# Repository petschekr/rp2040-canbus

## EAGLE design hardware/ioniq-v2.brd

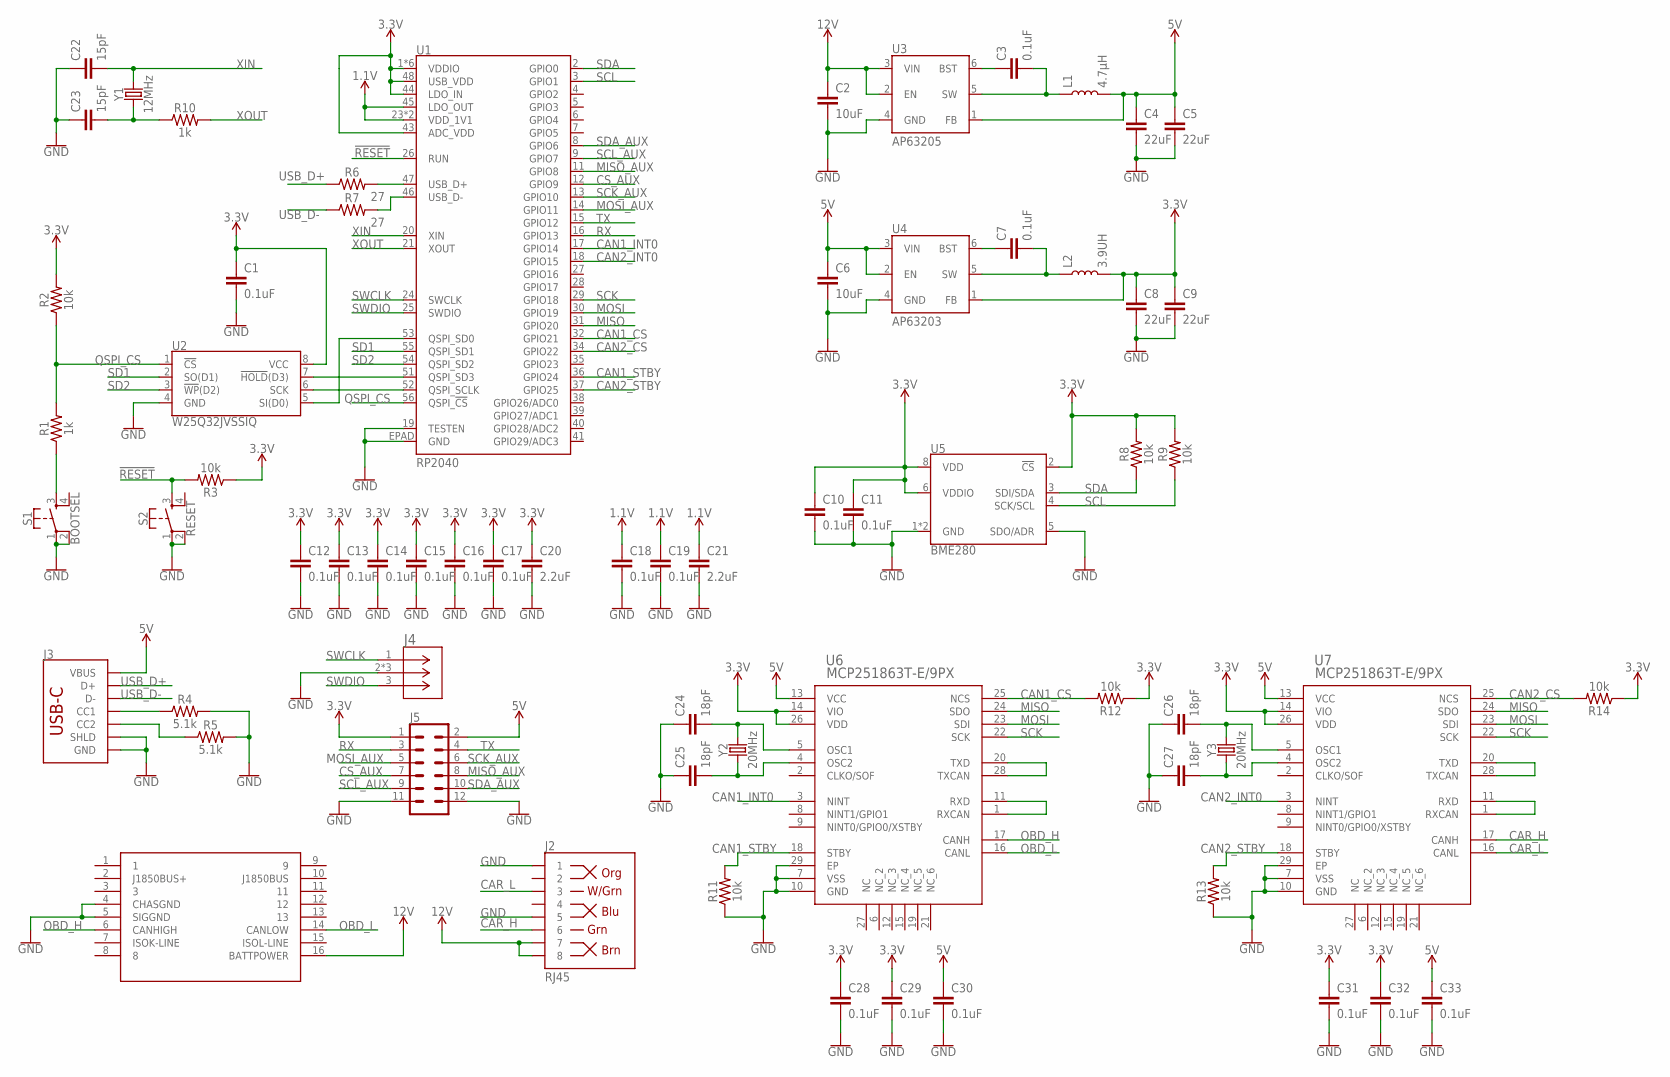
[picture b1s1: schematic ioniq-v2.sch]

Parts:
C1, C3, C7, C10, C11, C12, C13, C14, C15, C16, C17, C18, C19, C28, C29, C30, C31, C32, C33: 0.1uF; 0603
C2, C6: 10uF; 0805
C4, C5, C8, C9: 22uF; 0603
C20, C21: 2.2uF; 0603
C22, C23: 15pF; 0603
C24, C25, C26, C27: 18pF; 0603
J1: OBDII
J2: RJ45; RJ45-8
J3: USB_C_2-LAYER_PADS; USB-C-16P-2LAYER-PADS
J4: BM03B-SRSS-TB(LF)(SN); CONN_BM03B-SRSS-TB(LF)(SN)_JST
J5: 2X6 FEMALE; 2X6
L1: 4.7μH; INDUCTOR_4X4MM
L2: 3.9UH; INDUCTOR_3.9UH
R1, R10: 1k; 0603
R2, R3, R8, R9, R11, R12, R13, R14: 10k; 0603
R4, R5: 5.1k; 0603
R6, R7: 27; 0603
S1: BOOTSEL; TACTILE_SWITCH_SMD_4.6X2.8MM
S2: RESET; TACTILE_SWITCH_SMD_4.6X2.8MM
U1: RP2040; QFN-56
U2: W25Q32JVSSIQ; SOIC-8
U3: AP63205; SOT23-6
U4: AP63203; SOT23-6
U5: BME280; LGA-8-2.5X2.5
U6, U7: MCP251863T-E/9PX; VQFN28_9PX_3P25X3P25EPAD_MCH
Y1: 12MHz; CRYSTAL-SMD-3.2X2.5MM
Y2, Y3: 20MHz; CRYSTAL-SMD-3.2X2.5MM

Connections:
1.1V: C18.1, C19.1, C21.1, U1.23 (VDD_1V1), U1.45 (LDO_OUT), U1.50 (VDD_1V1)
3.3V: C1.1, C8.1, C9.1, C10.1, C11.1, C12.1, C13.1, C14.1, C15.1, C16.1, C17.1, C20.1, C28.1, C29.1, C31.1, C32.1, J5.1, L2.P$2 (2), R2.2, R3.1, R8.2, R9.2, R12.1, R14.1, U1.1 (VDDIO), U1.10 (VDDIO), U1.22 (VDDIO), U1.33 (VDDIO), U1.42 (VDDIO), U1.43 (ADC_VDD), U1.44 (LDO_IN), U1.48 (USB_VDD), U1.49 (VDDIO), U2.8 (VCC), U4.1 (FB), U5.2 (!CS), U5.6 (VDDIO), U5.8 (VDD), U6.14 (VIO), U6.26 (VDD), U7.14 (VIO), U7.26 (VDD)
5V: C4.1, C5.1, C6.1, C30.1, C33.1, J3.VBUS1 (VBUS), J3.VBUS2 (VBUS), J5.2, L1.P$2 (2), U3.1 (FB), U4.2 (EN), U4.3 (VIN), U6.13 (VCC), U7.13 (VCC)
12V: C2.1, J1.16 (BATTPOWER), J2.7, J2.8, U3.2 (EN), U3.3 (VIN)
!RESET: R3.2, S2.3, U1.26 (RUN)
CAN1_CS: R12.2, U1.32 (GPIO21), U6.25 (NCS)
CAN1_INT0: U1.17 (GPIO14), U6.3 (NINT)
CAN1_STBY: R11.2, U1.36 (GPIO24), U6.18 (STBY)
CAN2_CS: R14.2, U1.34 (GPIO22), U7.25 (NCS)
CAN2_INT0: U1.18 (GPIO15), U7.3 (NINT)
CAN2_STBY: R13.2, U1.37 (GPIO25), U7.18 (STBY)
CAR_H: J2.6, U7.17 (CANH)
CAR_L: J2.3, U7.16 (CANL)
CS_AUX: J5.7, U1.12 (GPIO9)
GND: C1.2, C2.2, C4.2, C5.2, C6.2, C8.2, C9.2, C10.2, C11.2, C12.2, C13.2, C14.2, C15.2, C16.2, C17.2, C18.2, C19.2, C20.2, C21.2, C22.1, C23.1, C24.1, C25.1, C26.1, C27.1, C28.2, C29.2, C30.2, C31.2, C32.2, C33.2, J1.4 (CHASGND), J1.5 (SIGGND), J2.1, J2.5, J3.GND, J3.GND2 (GND), J3.SHLD1 (SHLD), J3.SHLD2 (SHLD), J3.SHLD3 (SHLD), J3.SHLD4 (SHLD), J4.2, J4.4 (2), J4.5 (2), J5.11, J5.12, R4.2, R5.2, R11.1, R13.1, S1.1, S1.2, S2.1, S2.2, U1.19 (TESTEN), U1.EPAD (GND), U2.4 (GND), U3.4 (GND), U4.4 (GND), U5.1 (GND), U5.5 (SDO/ADR), U5.7 (GND), U6.7 (VSS), U6.10 (GND), U6.29 (EP), U7.7 (VSS), U7.10 (GND), U7.29 (EP)
MISO: U1.31 (GPIO20), U6.24 (SDO), U7.24 (SDO)
MISO_AUX: J5.8, U1.11 (GPIO8)
MOSI: U1.30 (GPIO19), U6.23 (SDI), U7.23 (SDI)
MOSI_AUX: J5.5, U1.14 (GPIO11)
unnamed: U1.52 (QSPI_SCLK), U2.6 (SCK)
unnamed: U1.51 (QSPI_SD3), U2.7 (!HOLD!(D3))
unnamed: U1.53 (QSPI_SD0), U2.5 (SI(D0))
unnamed: J3.A5 (CC1), R4.1
unnamed: C3.1, U3.6 (BST)
unnamed: C3.2, L1.P$1 (1), U3.5 (SW)
unnamed: J3.B5 (CC2), R5.1
unnamed: C7.1, U4.6 (BST)
unnamed: C7.2, L2.P$1 (1), U4.5 (SW)
unnamed: R7.2, U1.46 (USB_D-)
unnamed: R6.2, U1.47 (USB_D+)
unnamed: C23.2, R10.1, Y1.1
unnamed: R1.1, S1.3
unnamed: U6.20 (TXD), U6.28 (TXCAN)
unnamed: U6.1 (RXCAN), U6.11 (RXD)
unnamed: C24.2, U6.5 (OSC1), Y2.3 (2)
unnamed: C25.2, U6.4 (OSC2), Y2.1
unnamed: U7.1 (RXCAN), U7.11 (RXD)
unnamed: U7.20 (TXD), U7.28 (TXCAN)
unnamed: C26.2, U7.5 (OSC1), Y3.3 (2)
unnamed: C27.2, U7.4 (OSC2), Y3.1
OBD_H: J1.6 (CANHIGH), U6.17 (CANH)
OBD_L: J1.14 (CANLOW), U6.16 (CANL)
QSPI_CS: R1.2, R2.1, U1.56 (QSPI_!CS!), U2.1 (!CS!)
RX: J5.3, U1.16 (GPIO13)
SCK: U1.29 (GPIO18), U6.22 (SCK), U7.22 (SCK)
SCK_AUX: J5.6, U1.13 (GPIO10)
SCL: R9.1, U1.3 (GPIO1), U5.4 (SCK/SCL)
SCL_AUX: J5.9, U1.9 (GPIO7)
SD1: U1.55 (QSPI_SD1), U2.2 (SO(D1))
SD2: U1.54 (QSPI_SD2), U2.3 (!WP!(D2))
SDA: R8.1, U1.2 (GPIO0), U5.3 (SDI/SDA)
SDA_AUX: J5.10, U1.8 (GPIO6)
SWCLK: J4.1, U1.24 (SWCLK)
SWDIO: J4.3, U1.25 (SWDIO)
TX: J5.4, U1.15 (GPIO12)
USB_D+: J3.A6 (D+), J3.B6 (D+), R6.1
USB_D-: J3.A7 (D-), J3.B7 (D-), R7.1
XIN: C22.2, U1.20 (XIN), Y1.3 (2)
XOUT: R10.2, U1.21 (XOUT)

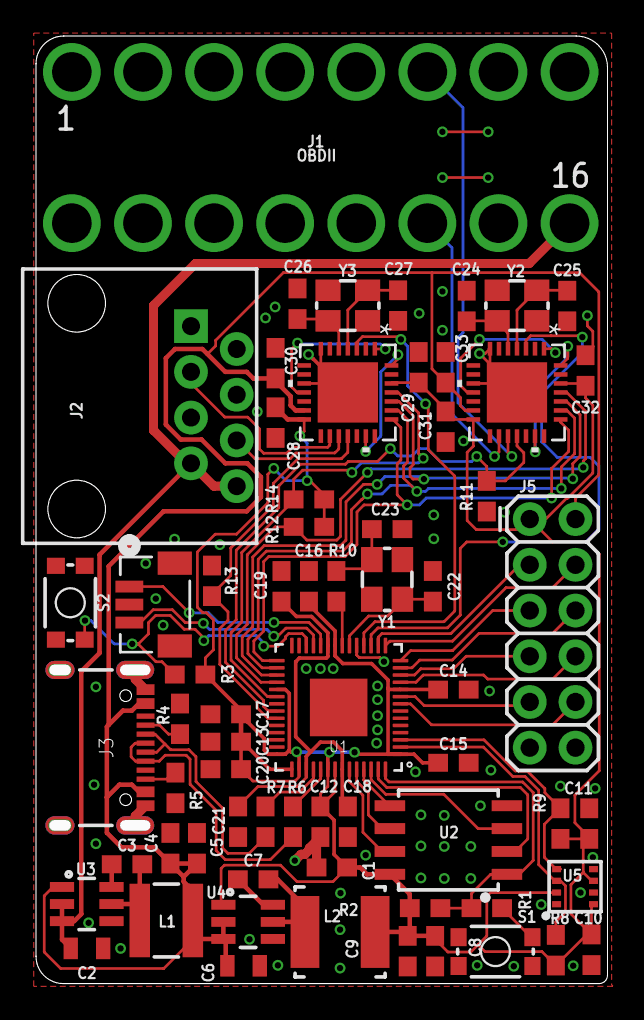
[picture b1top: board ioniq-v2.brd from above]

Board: 2 copper layers, 31.2 x 52.0 mm, 66 parts (0 on the bottom side), 59 nets.

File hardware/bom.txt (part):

Partlist exported from /home/petschekr/EAGLE/projects/ioniq-rp2040/ioniq-v2.sch at 11/4/24 4:37 AM

Part Value                 Device                                Package                        Description                                                                                                     COPYRIGHT                                                MANUFACTURER_PART_NUMBER MFR_NAME  PROD_ID    SF_ID     TYPE      VALUE     
C1   0.1uF                 0.1UF-0603-25V-10%-X7R-WE             0603                           0.1µF ceramic capacitors                                                                                                                                                                                    CAP-16503                      0.1uF     
C2   10uF                  10UF-0805-25V-10%                     0805                           10.0µF ceramic capacitors                                                                                                                                                                                   CAP-14259                      10uF      
C3   0.1uF                 0.1UF-0603-25V-5%                     0603                           0.1µF ceramic capacitors                                                                                                                                                                                    CAP-08604                      0.1uF     
C4   22uF                  22UF-0603-6.3V-20%                    0603                           22µF ceramic capacitors                                                                                                                                                                                     CAP-14464                      22uF      
C5   22uF                  22UF-0603-6.3V-20%                    0603                           22µF ceramic capacitors                                                                                                                                                                                     CAP-14464                      22uF      
C6   10uF                  10UF-0805-25V-10%                     0805                           10.0µF ceramic capacitors                                                                                                                                                                                   CAP-14259                      10uF      
C7   0.1uF                 0.1UF-0603-25V-5%                     0603                           0.1µF ceramic capacitors                                                                                                                                                                                    CAP-08604                      0.1uF     
C8   22uF                  22UF-0603-6.3V-20%                    0603                           22µF ceramic capacitors                                                                                                                                                                                     CAP-14464                      22uF      
C9   22uF                  22UF-0603-6.3V-20%                    0603                           22µF ceramic capacitors                                                                                                                                                                                     CAP-14464                      22uF      
C10  0.1uF                 0.1UF-0603-25V-10%-X7R-WE             0603                           0.1µF ceramic capacitors                                                                                                                                                                                    CAP-16503                      0.1uF     
C11  0.1uF                 0.1UF-0603-25V-10%-X7R-WE             0603                           0.1µF ceramic capacitors                                                                                                                                                                                    CAP-16503                      0.1uF     
C12  0.1uF                 0.1UF-0603-25V-10%-X7R-WE             0603                           0.1µF ceramic capacitors                                                                                                                                                                                    CAP-16503                      0.1uF     
C13  0.1uF                 0.1UF-0603-25V-10%-X7R-WE             0603                           0.1µF ceramic capacitors                                                                                                                                                                                    CAP-16503                      0.1uF     
C14  0.1uF                 0.1UF-0603-25V-10%-X7R-WE             0603                           0.1µF ceramic capacitors                                                                                                                                                                                    CAP-16503                      0.1uF     
C15  0.1uF                 0.1UF-0603-25V-10%-X7R-WE             0603                           0.1µF ceramic capacitors                                                                                                                                                                                    CAP-16503                      0.1uF     
C16  0.1uF                 0.1UF-0603-25V-10%-X7R-WE             0603                           0.1µF ceramic capacitors                                                                                                                                                                                    CAP-16503                      0.1uF     
C17  0.1uF                 0.1UF-0603-25V-10%-X7R-WE             0603                           0.1µF ceramic capacitors                                                                                                                                                                                    CAP-16503                      0.1uF     
C18  0.1uF                 0.1UF-0603-25V-10%-X7R-WE             0603                           0.1µF ceramic capacitors                                                                                                                                                                                    CAP-16503                      0.1uF     
C19  0.1uF                 0.1UF-0603-25V-10%-X7R-WE             0603                           0.1µF ceramic capacitors                                                                                                                                                                                    CAP-16503                      0.1uF     
C20  2.2uF                 2.2UF-0603-10V-20%                    0603                           2.2µF ceramic capacitors                                                                                                                                                                                    CAP-07888                      2.2uF     
C21  2.2uF                 2.2UF-0603-10V-20%                    0603                           2.2µF ceramic capacitors                                                                                                                                                                                    CAP-07888                      2.2uF     
C22  15pF                  15PF-0603-50V-5%                      0603                           15pF ceramic capacitors                                                                                                                                                                                     CAP-07881                      15pF      
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
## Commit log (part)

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2024-09-22 Working battery stats
2024-09-23 Update to use library setup/send/receive methods
2024-09-23 Tasks to demo forwarding battery info to the Comma RJ-45 port
2024-09-24 Serialize and send data over CAN to Comma
2024-09-26 Structure for making multiple queries to different ECUs
2024-09-27 Implement receiving queries from multiple ECUs simultaneously
2024-09-28 Send raw data over Comma CAN instead of partially parsing + add HVAC + add BME280 environmental data
2024-09-28 Improve ISO-TP logic to avoid deadlocks
2024-09-28 Implement ISO-TP timeout to prevent deadlocking
2024-09-29 Set up queries for all desired ECUs
2024-10-01 Poll the car less frequently when off
2024-10-05 Add dashboard query for odometer
2024-10-07 Add IGMP queries
2024-10-15 Decrease ignition off poll rate to once per 5 minutes and awake upon CAN 0 traffic
2024-10-16 Clear invalid transfers upon error
2024-11-04 Add hardware files
2024-11-22 Compensate measured temperature and humidity to a calibrated reference
2024-11-23 Keep quick polling for 60 seconds after car turns off Allows time for the car to update things into a consistent state after shutoff
2025-03-11 Keep quick polling while doors are unlocked or open

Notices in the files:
parts and their libraries:
SparkFun-Capacitors: Licensing: Creative Commons ShareAlike 4.0 International - https://creativecommons.org/licenses/by-sa/4.0
COPYRIGHT: Copyright (C) 2024 Ultra Librarian. All rights reserved.
